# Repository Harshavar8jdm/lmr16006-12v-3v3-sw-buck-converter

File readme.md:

readme_content = """# Ultra-Compact 12V to 3.3V Buck Converter Module (LMR16006)

An ultra-compact, high-efficiency step-down (buck) DC-DC converter breakout board designed using Texas Instruments' **LMR16006XDDCR** synchronous buck regulator. This board steps down a nominal 12V DC input (supports up to 60V) to a regulated 3.3V DC output, making it ideal for powering 3.3V microcontrollers (ESP32, STM32, RP2040) and sensors in space-constrained embedded systems and automotive projects.

---

## 📷 Board Preview

| Top View (3D Render) | Bottom View (3D Render) |
| :---: | :---: |
|  |  |

---

## ✨ Key Features

- **Ultra-Compact Form Factor:** Tiny **20 mm x 15 mm** footprint with standard 2.54 mm (100 mil) header pins for breadboard integration or carrier board mounting.
- **Wide Input Voltage Range:** Supports $4.2\text{V}$ to $60\text{V}$ input range (configured and tested for 12V step-down).
- **High Efficiency & High Frequency:** $700\text{kHz}$ switching frequency allows the use of small surface-mount inductors and capacitors.
- **Optimized High-Current Loop:** Minimal $di/dt$ switching loop area to suppress high-frequency ringing and electromagnetic interference (EMI).
- **Thermal & Grounding Integrity:** Multi-via stitch arrays on high-power thermal pads (Schottky diode anode and IC GND) to ensure efficient heat dissipation into the bottom ground plane.
- **Truncated SW Polygon:** Reduced copper switching node ($SW$) area to prevent parasitic capacitive radiation.

---

## 📐 Circuit Schematic & Calculations

### 1. Output Voltage Selection
The output voltage is configured using a precision feedback resistor divider ($R_2$ and $R_3$) connected to the $FB$ pin ($V_{FB} = 0.765\text{V}$):

$$V_{OUT} = V_{FB} \times \\left(1 + \\frac{R_2}{R_3}\\right)$$

Using standard 1% tolerance resistors:
- $R_2 = 33.2\\text{ k}\\Omega$
- $R_3 = 10.0\\text{ k}\\Omega$

$$V_{OUT} = 0.765\\text{V} \\times \\left(1 + \\frac{33.2\\text{ k}\\Omega}{10.0\\text{ k}\\Omega}\\right) = 0.765\\text{V} \\times 4.32 = \\mathbf{3.305\\text{V}}$$

### 2. Inductor & Switching Selection
- **Inductor ($L_1$):** $6.8\\mu\\text{H}$ power inductor rated for target load current and peak switching ripple.
- **Bootstrap Capacitor ($C_1$):** $100\\text{nF}$ ceramic capacitor driving the internal high-side MOSFET gate driver.
- **Shutdown / Enable ($R_1$):** $100\\text{k}\\Omega$ pull-up resistor tying $SHDN$ to $VIN$ for automatic power-on operation.

---

## 🖼️ PCB Layout & Stackup

### Layout Highlights:
1. **Compact Power Loop:** $C_2$ ($C_{IN}$), $U_1$ ($VIN/SW$), and $D_1$ are placed immediately adjacent to each other to minimize high-frequency AC loop area.
2. **EMI Mitigation:** The SW node copper pour (`Net-(D1-K)`) is tightly constrained to component pads to eliminate unshielded antenna radiation.
3. **Thermal Vias:** A $3\\times 3$ via matrix under the $D_1$ ground pad along with ground stitching around $U_1$ effectively passes heat to the full bottom ground plane layer.
4. **Isolated Feedback Path:** The high-impedance feedback net ($FB$) is routed away from the noisy switching node and inductor body.

---

## 🛒 Bill of Materials (BOM)

| Designator | Quantity | Value / Part Number | Footprint | Description |
| :--- | :---: | :--- | :--- | :--- |
| **U1** | 1 | LMR16006XDDCR | SOT-23-6 (DDC) | 0.6A, 60V, 700kHz Step-Down Regulator |
| **L1** | 1 | 6.8 µH | 4040 / Shielded | Power Inductor |
| **D1** | 1 | Schottky Diode (e.g., B140/SS14) | SMA / SMB | Free-wheeling Catch Diode |
| **C1** | 1 | 100 nF, 50V | 0603 | Bootstrap Capacitor (X7R) |
| **C2** | 1 | 2.2 µF – 10 µF, 50V | 0805 / 1206 | Input Filter Capacitor (X7R) |
| **C3** | 1 | 22 µF, 10V | 0805 | Output Filter Capacitor (X7R) |
| **R1** | 1 | 100 kΩ | 0603 | Shutdown Pull-up Resistor |
| **R2** | 1 | 33.2 kΩ (1%) | 0603 | Feedback Upper Resistor |
| **R3** | 1 | 10.0 kΩ (1%) | 0603 | Feedback Lower Resistor |
| **J1 – J4** | 4 | 1x1 Pin Header | 2.54 mm pitch | Board Power Contacts (12V, GND, 3.3V, GND) |

---

## 🏭 Fabrication Parameters

- **Board Dimensions:** $20\\text{ mm} \\times 15\\text{ mm}$
- **Layer Count:** 2 Layers
- **PCB Thickness:** 1.6 mm
- **Copper Weight:** 1 oz (35 µm)
- **Minimum Trace / Clearance:** 0.25 mm / 0.2 mm
- **Solder Mask Color:** Green (or preferred)
- **Silkscreen:** White

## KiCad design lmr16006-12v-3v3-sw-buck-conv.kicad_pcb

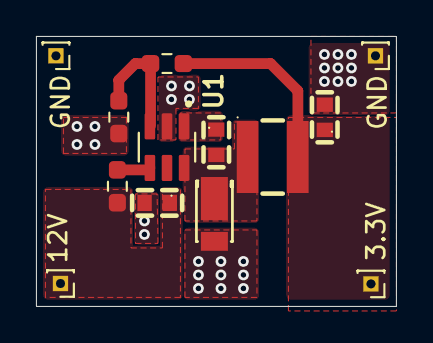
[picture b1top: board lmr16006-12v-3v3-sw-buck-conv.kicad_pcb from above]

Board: 2 copper layers, 20.0 x 15.0 mm, 13 parts (0 on the bottom side), 7 nets.

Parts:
3.3V, 12V: Conn_01x01_Pin; PinHeader_1x01_P1.00mm_Vertical
C1: 100nF; C0603_VJ0603Y104JXQCW1BC_C3834925
C2: 2.2uF; C0603_CL10A225KL8NNNC_C307463
C3: 22uF; C0603_TCC0603X5R226K100CT_C53032012
D1: D_Schottky; POWERDI-123_L2_8-W1_8-LS3_7-RD-1_SS14FP_C894423
GND: Conn_01x01_Pin; PinHeader_1x01_P1.00mm_Vertical
GND#2: Conn_01x01_Pin; PinHeader_1x01_P1.00mm_Vertical
L1: 6.8uH; IND-SMD_L4_0-W4_0_NRS4018T_NRS4018T6R8MDGJ_C222881
R1: 100K; R_0603_1608Metric_Pad0.98x0.95mm_HandSolder
R2: 33.2K; R_0603_1608Metric_Pad0.98x0.95mm_HandSolder
R3: 10K; R_0603_1608Metric_Pad0.98x0.95mm_HandSolder
U1: LMR16006XDDCR; SOT95P280X110-6N

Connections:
+3.3V: 3.3V.1 (Pin_1_1), C3.1, L1.2, R2.1
GND: C2.2, C3.2, D1.2 (A), GND.1 (Pin_1_1), GND#2.1 (Pin_1_1), R3.2, U1.2 (GND)
unnamed: C1.2, D1.1 (K), L1.1, U1.6 (SW)
unnamed: C1.1, U1.1 (CB)
unnamed: R2.2, R3.1, U1.3 (FB)
unnamed: R1.2, U1.4 (SHDN)
VIN: 12V.1 (Pin_1_1), C2.1, R1.1, U1.5 (VIN)

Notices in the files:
readme.md:
License: MIT
